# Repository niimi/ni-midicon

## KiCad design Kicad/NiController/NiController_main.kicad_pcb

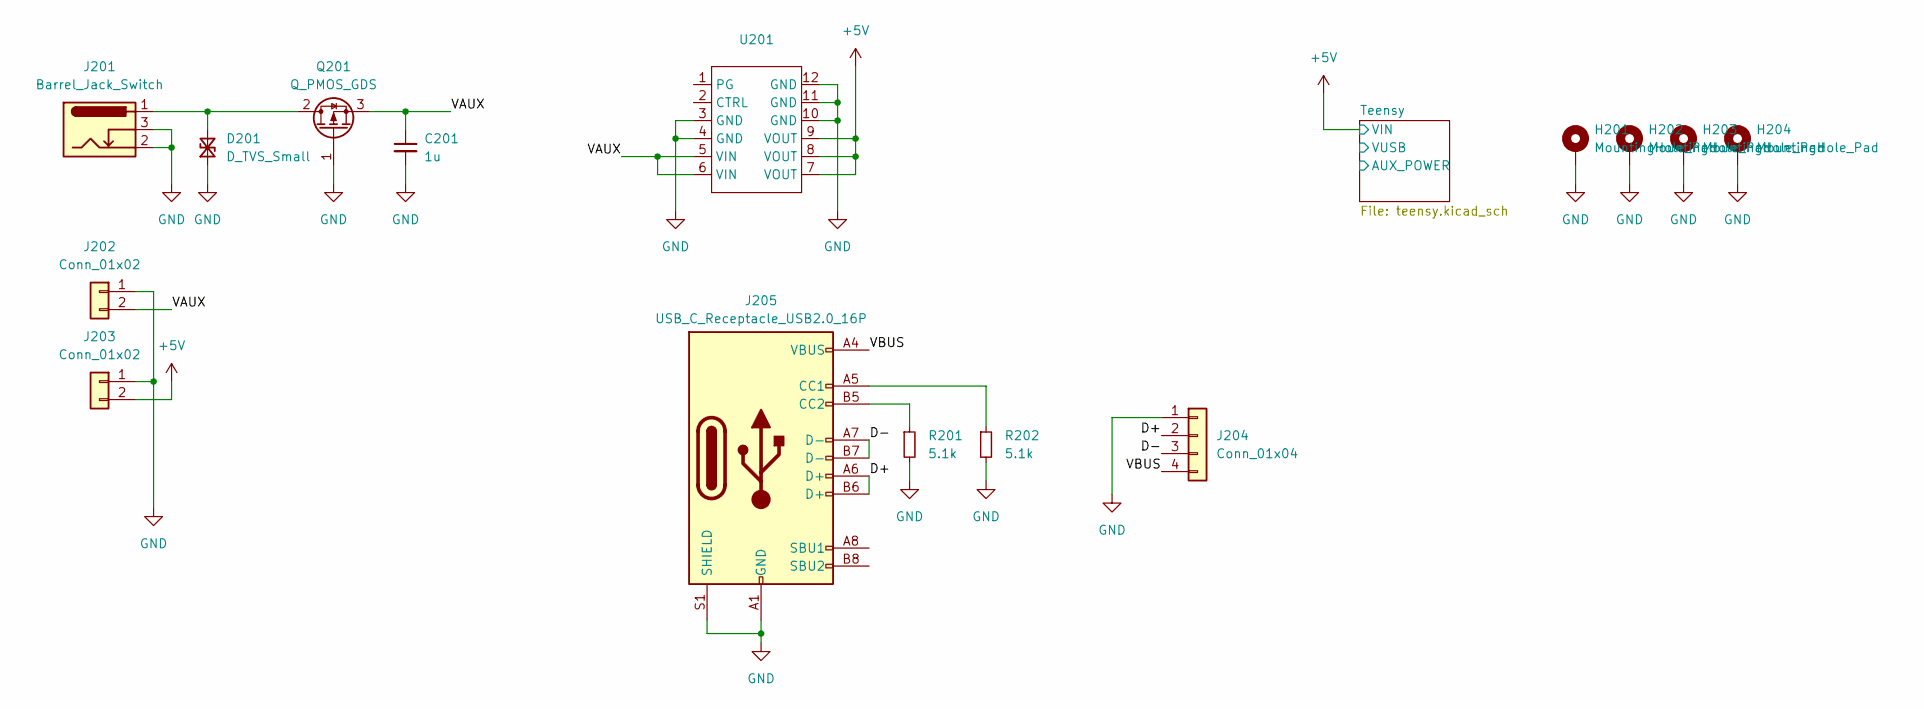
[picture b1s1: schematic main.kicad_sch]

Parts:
C201: 1u; C_0603_1608Metric
D201: D_TVS_Small; D_SOD-523
H201, H202, H203, H204: MountingHole_Pad; MountingHole_2.5mm_Pad_Via
J201: Barrel_Jack_Switch; BarrelJack_Horizontal
J202, J203: Conn_01x02; PinHeader_1x02_P2.54mm_Vertical
J204: Conn_01x04; PinSocket_1x04_P2.54mm_Vertical
J205: USB_C_Receptacle_USB2.0_16P; USB_C_Receptacle_G-Switch_GT-USB-7010ASV
Q201: Q_PMOS_GDS; TO-252-2
R201, R202: 5.1k; R_0603_1608Metric
U201: AE-MYMGK00506ERSR-5V0

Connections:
+5V: J203.2, U201.7 (VOUT), U201.8 (VOUT), U201.9 (VOUT); also elsewhere on the board
/main/D+: J204.2, J205.A6 (D+), J205.B6 (D+)
/main/D-: J204.3, J205.A7 (D-), J205.B7 (D-)
/main/VAUX: C201.1, J202.2, Q201.3 (S), U201.5 (VIN), U201.6 (VIN)
/main/VBUS: J204.4, J205.A4 (VBUS), J205.A9 (VBUS), J205.B4 (VBUS), J205.B9 (VBUS)
GND: C201.2, D201.1 (A1), H201.1, H202.1, H203.1, H204.1, J201.2, J201.3, J202.1, J203.1, J204.1, J205.A1 (GND), J205.A12 (GND), J205.B1 (GND), J205.B12 (GND), J205.S1 (SHIELD), Q201.1 (G), R201.2, R202.2, U201.3 (GND), U201.4 (GND), U201.10 (GND), U201.11 (GND), U201.12 (GND); also elsewhere on the board
unnamed: D201.2 (A2), J201.1, Q201.2 (D)
unnamed: J205.A5 (CC1), R202.1
unnamed: J205.B5 (CC2), R201.1

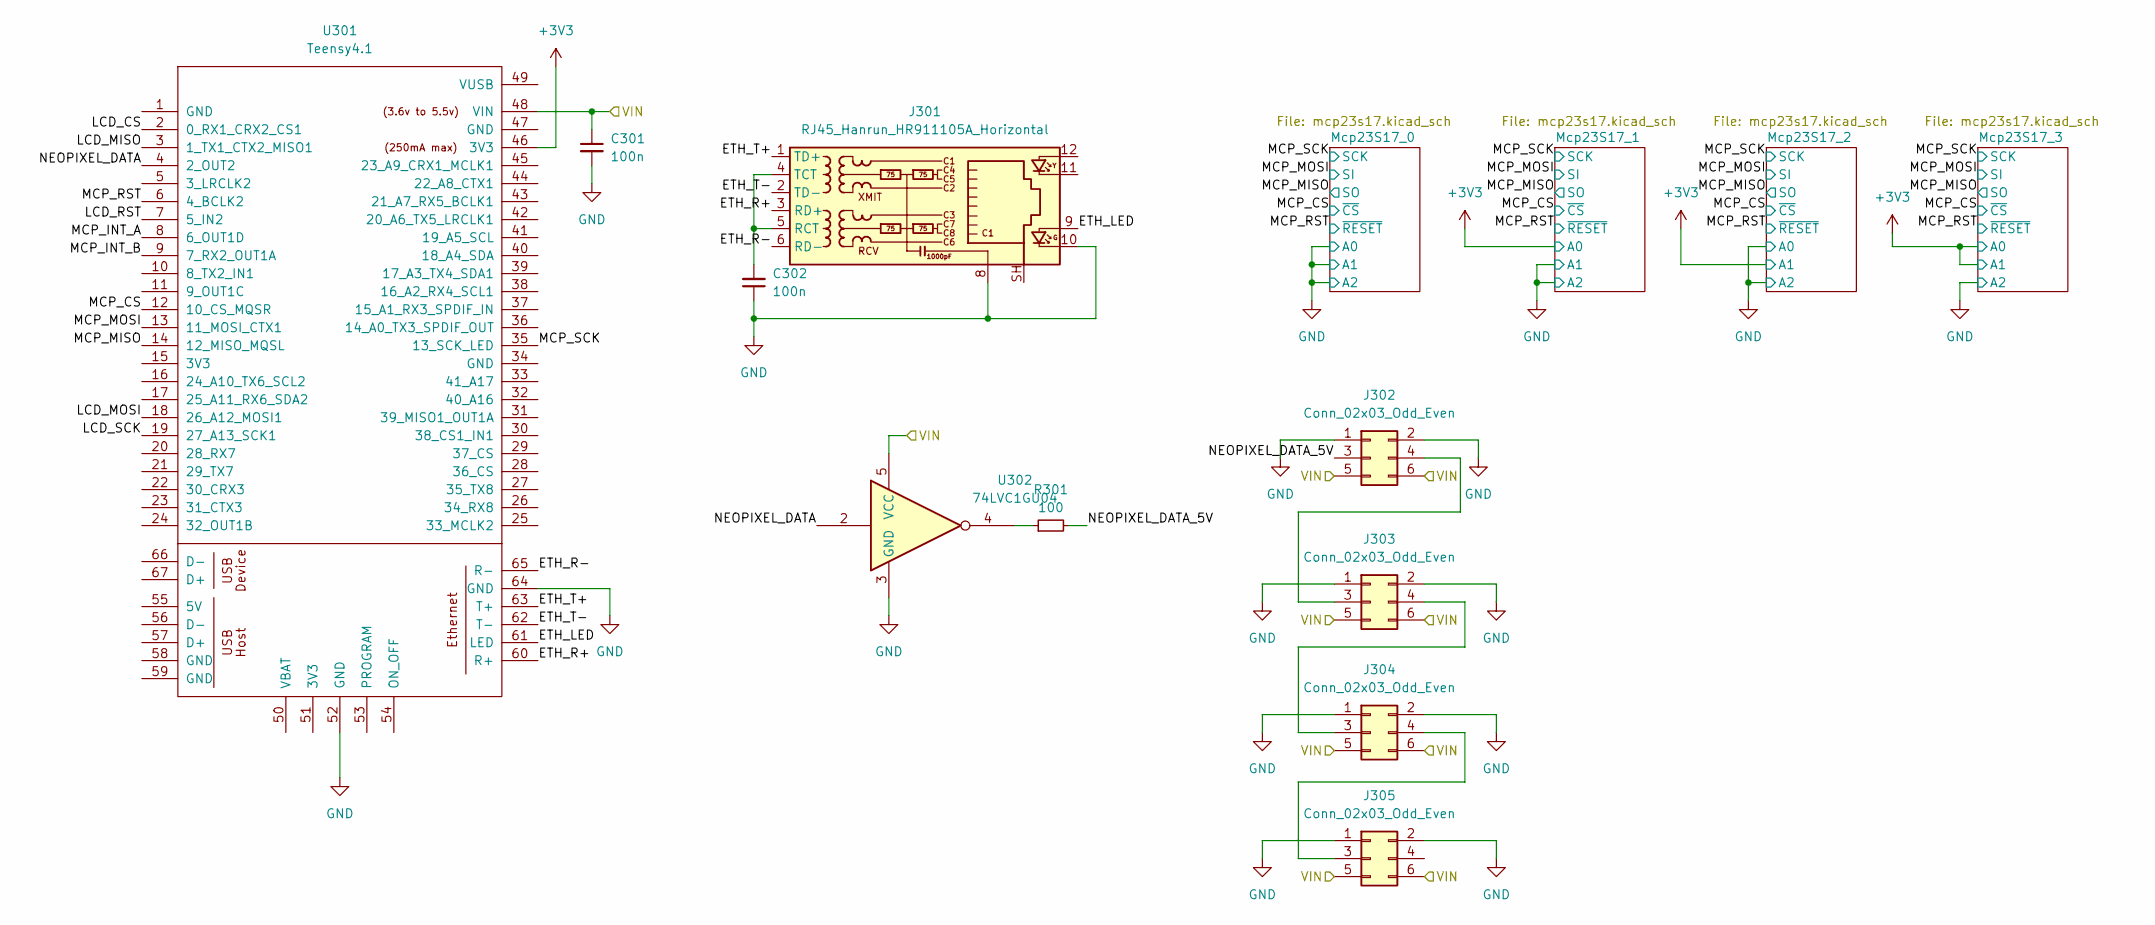
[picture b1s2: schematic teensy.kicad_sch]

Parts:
C301, C302: 100n; C_0603_1608Metric
J301: RJ45_Hanrun_HR911105A_Horizontal
J302, J303, J304, J305: Conn_02x03_Odd_Even; IDC-Header_2x03_P2.54mm_Vertical
R301: 100; R_0603_1608Metric
U301: Teensy4.1; Teensy41
U302: 74LVC1GU04; SOT-353_SC-70-5

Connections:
+3V3: U301.46 (3V3); also elsewhere on the board
+5V: C301.1, J302.5, J302.6, J303.5, J303.6, J304.5, J304.6, J305.5, J305.6, U301.48 (VIN), U302.5 (VCC); also elsewhere on the board
/main/Teensy/ETH_LED: J301.9, U301.61 (LED)
/main/Teensy/ETH_R+: J301.3 (RD+), U301.60 (R+)
/main/Teensy/ETH_R-: J301.6 (RD-), U301.65 (R-)
/main/Teensy/ETH_T+: J301.1 (TD+), U301.63 (T+)
/main/Teensy/ETH_T-: J301.2 (TD-), U301.62 (T-)
/main/Teensy/LCD_CS: U301.2 (0_RX1_CRX2_CS1)
/main/Teensy/LCD_MISO: U301.3 (1_TX1_CTX2_MISO1)
/main/Teensy/LCD_MOSI: U301.18 (26_A12_MOSI1)
/main/Teensy/LCD_RST: U301.7 (5_IN2)
/main/Teensy/LCD_SCK: U301.19 (27_A13_SCK1)
/main/Teensy/MCP_CS: U301.12 (10_CS_MQSR); also elsewhere on the board
/main/Teensy/MCP_INT_A: U301.8 (6_OUT1D)
/main/Teensy/MCP_INT_B: U301.9 (7_RX2_OUT1A)
/main/Teensy/MCP_MISO: U301.14 (12_MISO_MQSL); also elsewhere on the board
/main/Teensy/MCP_MOSI: U301.13 (11_MOSI_CTX1); also elsewhere on the board
/main/Teensy/MCP_RST: U301.6 (4_BCLK2); also elsewhere on the board
/main/Teensy/MCP_SCK: U301.35 (13_SCK_LED); also elsewhere on the board
/main/Teensy/NEOPIXEL_DATA: U301.4 (2_OUT2), U302.2
/main/Teensy/NEOPIXEL_DATA_5V: J302.3, R301.2
GND: C301.2, C302.1, J301.8, J301.10, J302.1, J302.2, J303.1, J303.2, J304.1, J304.2, J305.1, J305.2, U301.52 (GND), U301.64 (GND), U302.3 (GND); also elsewhere on the board
unnamed: C302.2, J301.4 (TCT), J301.5 (RCT)
unnamed: J302.4, J303.3
unnamed: J303.4, J304.3
unnamed: J304.4, J305.3
unnamed: R301.1, U302.4

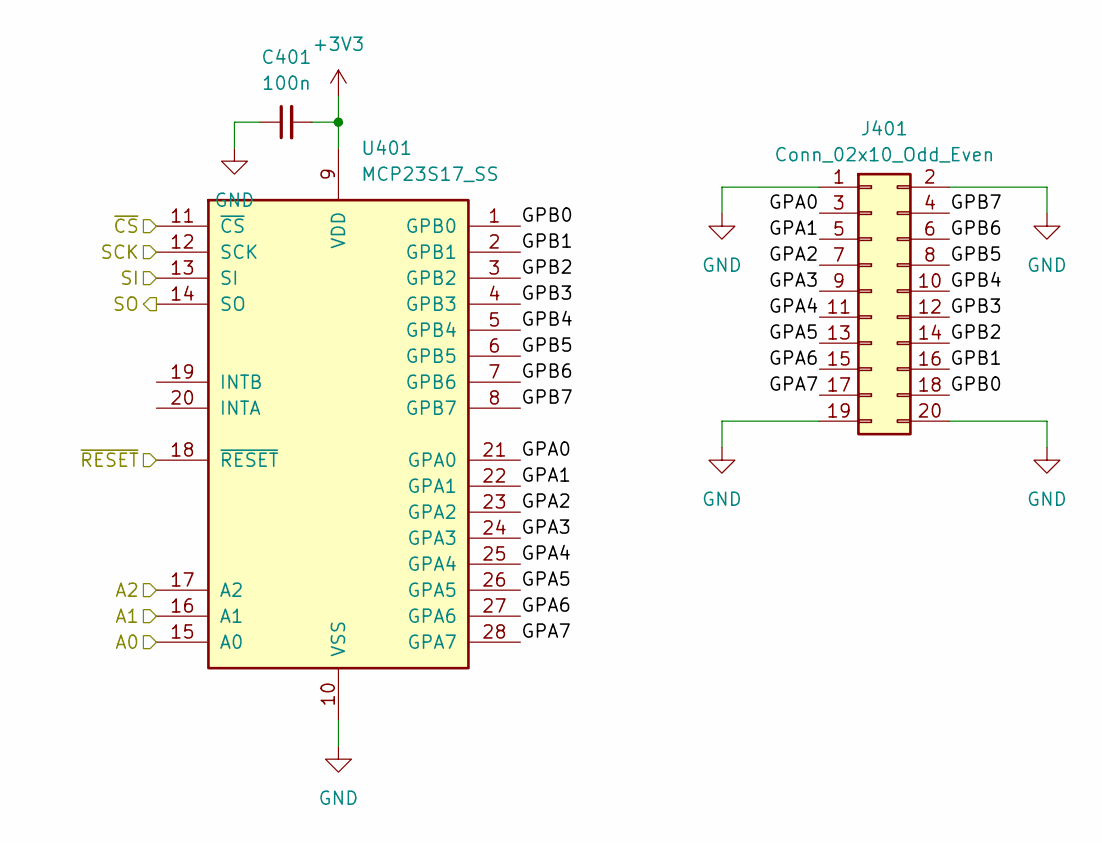
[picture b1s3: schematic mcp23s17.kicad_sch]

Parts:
C401: 100n; C_0603_1608Metric
J401: Conn_02x10_Odd_Even; IDC-Header_2x10_P2.54mm_Vertical
U401: MCP23S17_SS; SSOP-28_5.3x10.2mm_P0.65mm

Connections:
+3V3: C401.2, U401.9 (VDD); also elsewhere on the board
/main/Teensy/MCP_CS: U401.11 (~CS); also elsewhere on the board
/main/Teensy/MCP_MISO: U401.14 (SO); also elsewhere on the board
/main/Teensy/MCP_MOSI: U401.13 (SI); also elsewhere on the board
/main/Teensy/MCP_RST: U401.18 (~RESET); also elsewhere on the board
/main/Teensy/MCP_SCK: U401.12 (SCK); also elsewhere on the board
/main/Teensy/Mcp23S17_0/GPA0: J401.3, U401.21 (GPA0)
/main/Teensy/Mcp23S17_0/GPA1: J401.5, U401.22 (GPA1)
/main/Teensy/Mcp23S17_0/GPA2: J401.7, U401.23 (GPA2)
/main/Teensy/Mcp23S17_0/GPA3: J401.9, U401.24 (GPA3)
/main/Teensy/Mcp23S17_0/GPA4: J401.11, U401.25 (GPA4)
/main/Teensy/Mcp23S17_0/GPA5: J401.13, U401.26 (GPA5)
/main/Teensy/Mcp23S17_0/GPA6: J401.15, U401.27 (GPA6)
/main/Teensy/Mcp23S17_0/GPA7: J401.17, U401.28 (GPA7)
/main/Teensy/Mcp23S17_0/GPB0: J401.18, U401.1 (GPB0)
/main/Teensy/Mcp23S17_0/GPB1: J401.16, U401.2 (GPB1)
/main/Teensy/Mcp23S17_0/GPB2: J401.14, U401.3 (GPB2)
/main/Teensy/Mcp23S17_0/GPB3: J401.12, U401.4 (GPB3)
/main/Teensy/Mcp23S17_0/GPB4: J401.10, U401.5 (GPB4)
/main/Teensy/Mcp23S17_0/GPB5: J401.8, U401.6 (GPB5)
/main/Teensy/Mcp23S17_0/GPB6: J401.6, U401.7 (GPB6)
/main/Teensy/Mcp23S17_0/GPB7: J401.4, U401.8 (GPB7)
GND: C401.1, J401.1, J401.2, J401.19, J401.20, U401.10 (VSS), U401.15 (A0), U401.16 (A1), U401.17 (A2); also elsewhere on the board

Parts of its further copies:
C501, C601, C701: 100n; C_0603_1608Metric
J501, J601, J701: Conn_02x10_Odd_Even; IDC-Header_2x10_P2.54mm_Vertical
U501, U601, U701: MCP23S17_SS; SSOP-28_5.3x10.2mm_P0.65mm

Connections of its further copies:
+3V3: C501.2, C601.2, C701.2, U501.9 (VDD), U501.15 (A0), U601.9 (VDD), U601.16 (A1), U701.9 (VDD), U701.15 (A0), U701.16 (A1); also elsewhere on the board
/main/Teensy/MCP_CS: U501.11 (~CS), U601.11 (~CS), U701.11 (~CS); also elsewhere on the board
/main/Teensy/MCP_MISO: U501.14 (SO), U601.14 (SO), U701.14 (SO); also elsewhere on the board
/main/Teensy/MCP_MOSI: U501.13 (SI), U601.13 (SI), U701.13 (SI); also elsewhere on the board
/main/Teensy/MCP_RST: U501.18 (~RESET), U601.18 (~RESET), U701.18 (~RESET); also elsewhere on the board
/main/Teensy/MCP_SCK: U501.12 (SCK), U601.12 (SCK), U701.12 (SCK); also elsewhere on the board
/main/Teensy/Mcp23S17_1/GPA0: J501.3, U501.21 (GPA0)
/main/Teensy/Mcp23S17_1/GPA1: J501.5, U501.22 (GPA1)
/main/Teensy/Mcp23S17_1/GPA2: J501.7, U501.23 (GPA2)
/main/Teensy/Mcp23S17_1/GPA3: J501.9, U501.24 (GPA3)
/main/Teensy/Mcp23S17_1/GPA4: J501.11, U501.25 (GPA4)
/main/Teensy/Mcp23S17_1/GPA5: J501.13, U501.26 (GPA5)
/main/Teensy/Mcp23S17_1/GPA6: J501.15, U501.27 (GPA6)
/main/Teensy/Mcp23S17_1/GPA7: J501.17, U501.28 (GPA7)
/main/Teensy/Mcp23S17_1/GPB0: J501.18, U501.1 (GPB0)
/main/Teensy/Mcp23S17_1/GPB1: J501.16, U501.2 (GPB1)
/main/Teensy/Mcp23S17_1/GPB2: J501.14, U501.3 (GPB2)
/main/Teensy/Mcp23S17_1/GPB3: J501.12, U501.4 (GPB3)
/main/Teensy/Mcp23S17_1/GPB4: J501.10, U501.5 (GPB4)
/main/Teensy/Mcp23S17_1/GPB5: J501.8, U501.6 (GPB5)
/main/Teensy/Mcp23S17_1/GPB6: J501.6, U501.7 (GPB6)
/main/Teensy/Mcp23S17_1/GPB7: J501.4, U501.8 (GPB7)
/main/Teensy/Mcp23S17_2/GPA0: J601.3, U601.21 (GPA0)
/main/Teensy/Mcp23S17_2/GPA1: J601.5, U601.22 (GPA1)
/main/Teensy/Mcp23S17_2/GPA2: J601.7, U601.23 (GPA2)
/main/Teensy/Mcp23S17_2/GPA3: J601.9, U601.24 (GPA3)
/main/Teensy/Mcp23S17_2/GPA4: J601.11, U601.25 (GPA4)
/main/Teensy/Mcp23S17_2/GPA5: J601.13, U601.26 (GPA5)
/main/Teensy/Mcp23S17_2/GPA6: J601.15, U601.27 (GPA6)
/main/Teensy/Mcp23S17_2/GPA7: J601.17, U601.28 (GPA7)
/main/Teensy/Mcp23S17_2/GPB0: J601.18, U601.1 (GPB0)
/main/Teensy/Mcp23S17_2/GPB1: J601.16, U601.2 (GPB1)
/main/Teensy/Mcp23S17_2/GPB2: J601.14, U601.3 (GPB2)
/main/Teensy/Mcp23S17_2/GPB3: J601.12, U601.4 (GPB3)
/main/Teensy/Mcp23S17_2/GPB4: J601.10, U601.5 (GPB4)
/main/Teensy/Mcp23S17_2/GPB5: J601.8, U601.6 (GPB5)
/main/Teensy/Mcp23S17_2/GPB6: J601.6, U601.7 (GPB6)
/main/Teensy/Mcp23S17_2/GPB7: J601.4, U601.8 (GPB7)
/main/Teensy/Mcp23S17_3/GPA0: J701.3, U701.21 (GPA0)
/main/Teensy/Mcp23S17_3/GPA1: J701.5, U701.22 (GPA1)
/main/Teensy/Mcp23S17_3/GPA2: J701.7, U701.23 (GPA2)
/main/Teensy/Mcp23S17_3/GPA3: J701.9, U701.24 (GPA3)
/main/Teensy/Mcp23S17_3/GPA4: J701.11, U701.25 (GPA4)
/main/Teensy/Mcp23S17_3/GPA5: J701.13, U701.26 (GPA5)
/main/Teensy/Mcp23S17_3/GPA6: J701.15, U701.27 (GPA6)
/main/Teensy/Mcp23S17_3/GPA7: J701.17, U701.28 (GPA7)
/main/Teensy/Mcp23S17_3/GPB0: J701.18, U701.1 (GPB0)
/main/Teensy/Mcp23S17_3/GPB1: J701.16, U701.2 (GPB1)
/main/Teensy/Mcp23S17_3/GPB2: J701.14, U701.3 (GPB2)
/main/Teensy/Mcp23S17_3/GPB3: J701.12, U701.4 (GPB3)
/main/Teensy/Mcp23S17_3/GPB4: J701.10, U701.5 (GPB4)
/main/Teensy/Mcp23S17_3/GPB5: J701.8, U701.6 (GPB5)
/main/Teensy/Mcp23S17_3/GPB6: J701.6, U701.7 (GPB6)
/main/Teensy/Mcp23S17_3/GPB7: J701.4, U701.8 (GPB7)
GND: C501.1, C601.1, C701.1, J501.1, J501.2, J501.19, J501.20, J601.1, J601.2, J601.19, J601.20, J701.1, J701.2, J701.19, J701.20, U501.10 (VSS), U501.16 (A1), U501.17 (A2), U601.10 (VSS), U601.15 (A0), U601.17 (A2), U701.10 (VSS), U701.17 (A2); also elsewhere on the board

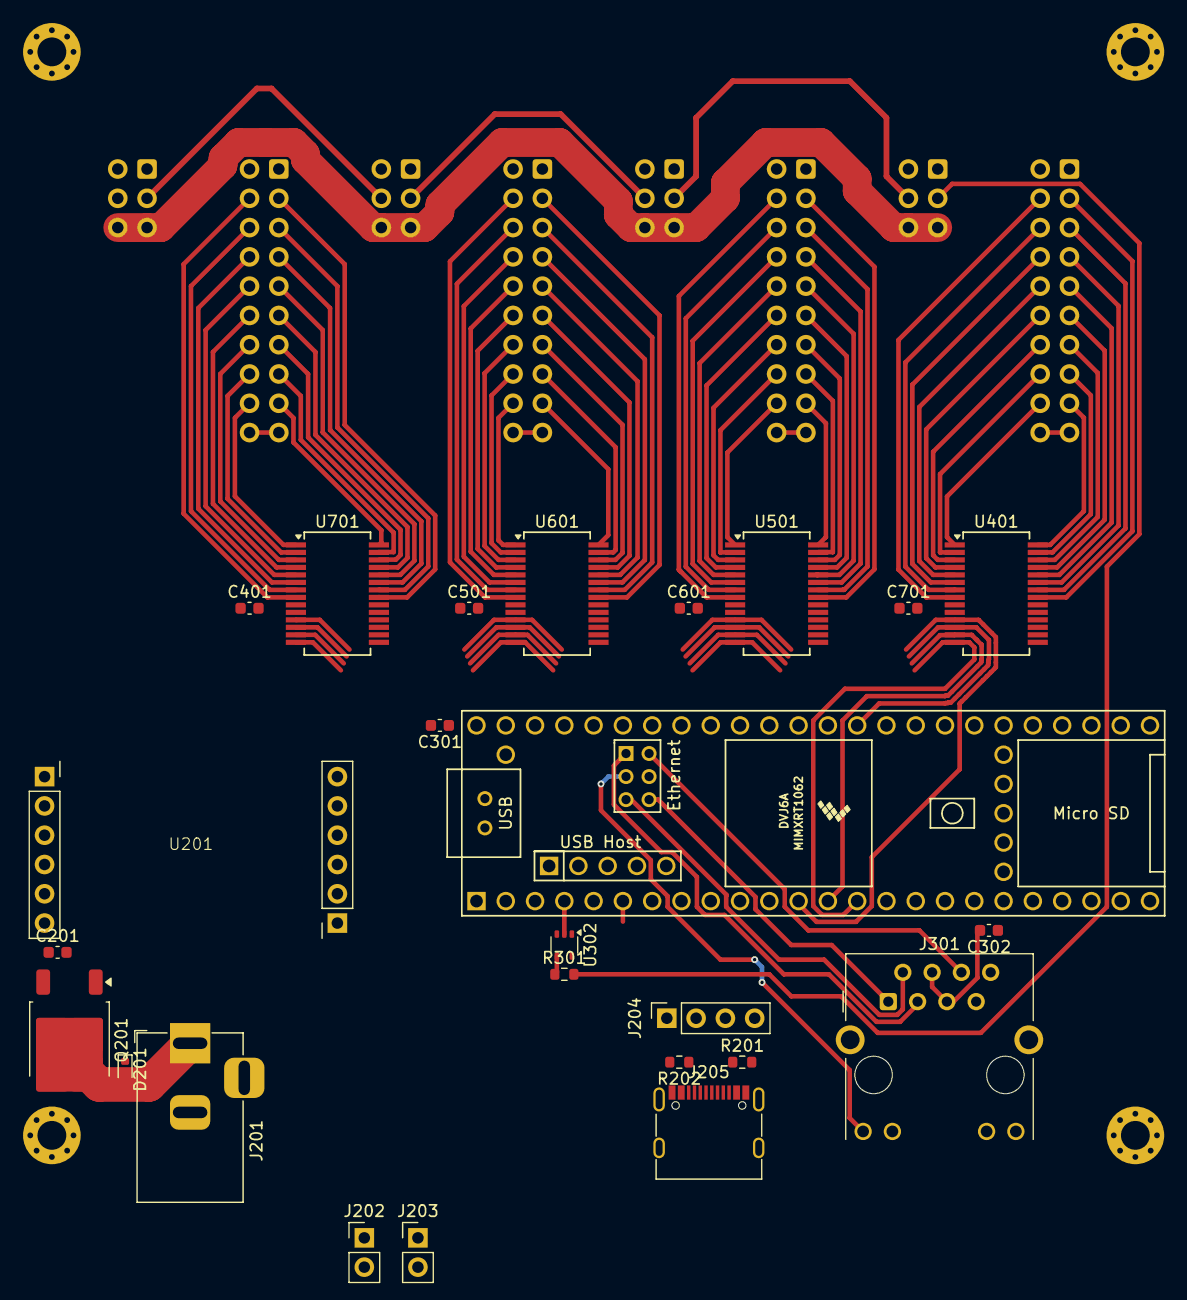
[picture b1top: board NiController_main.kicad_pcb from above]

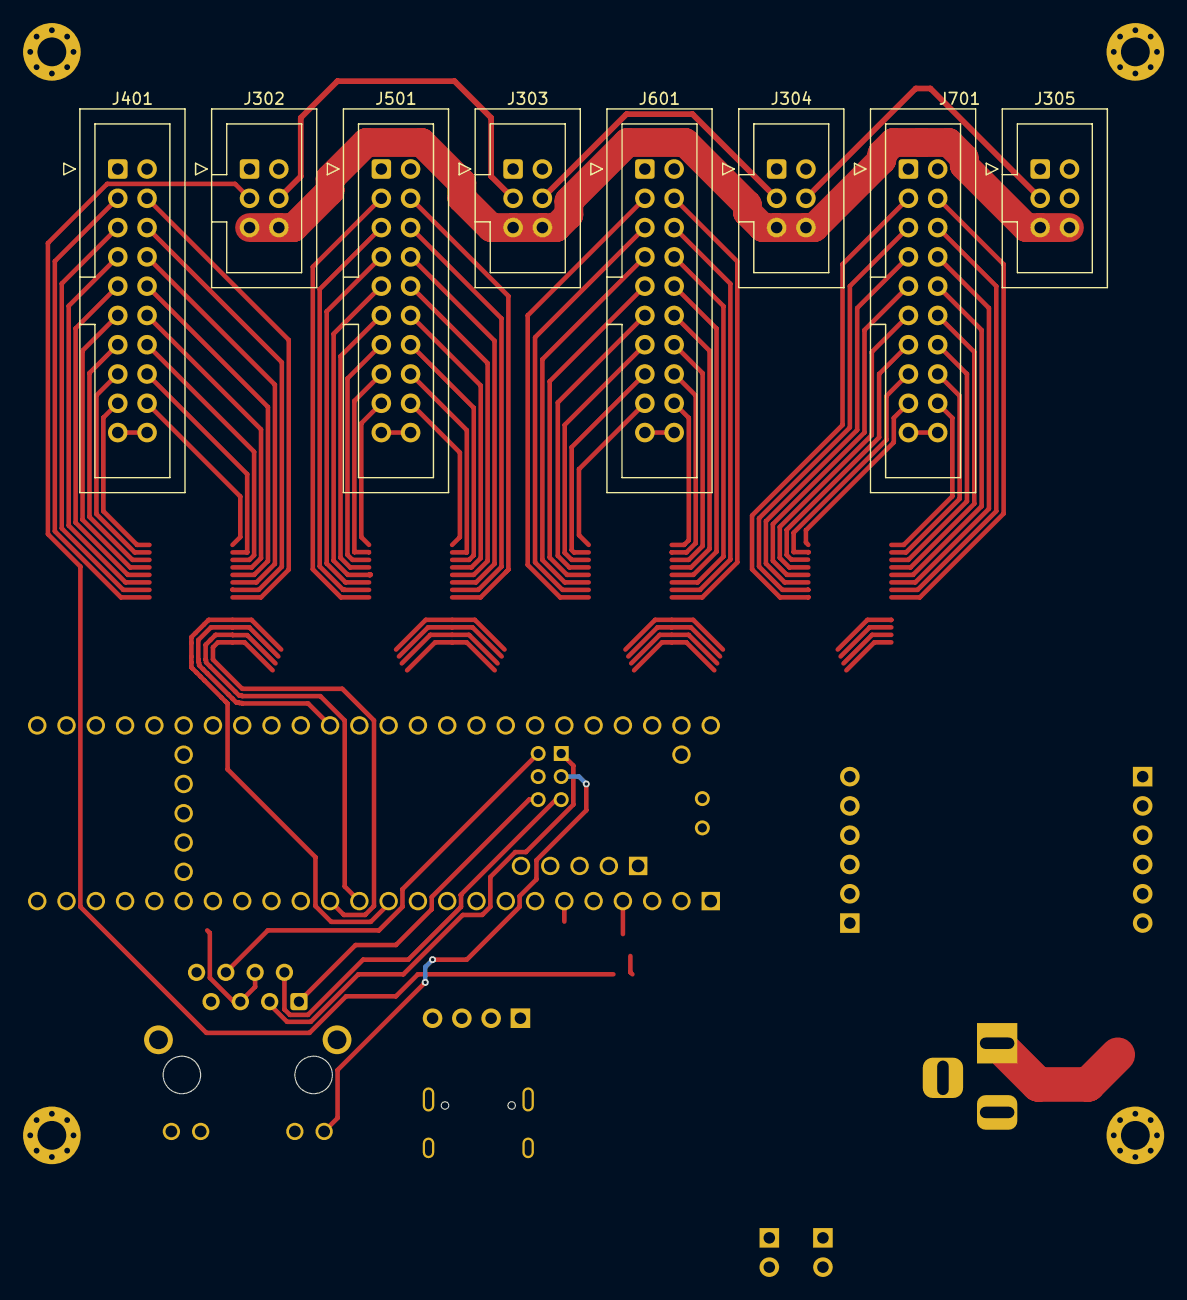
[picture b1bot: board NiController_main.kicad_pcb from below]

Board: 2 copper layers, 37 parts (8 on the bottom side), 91 nets.

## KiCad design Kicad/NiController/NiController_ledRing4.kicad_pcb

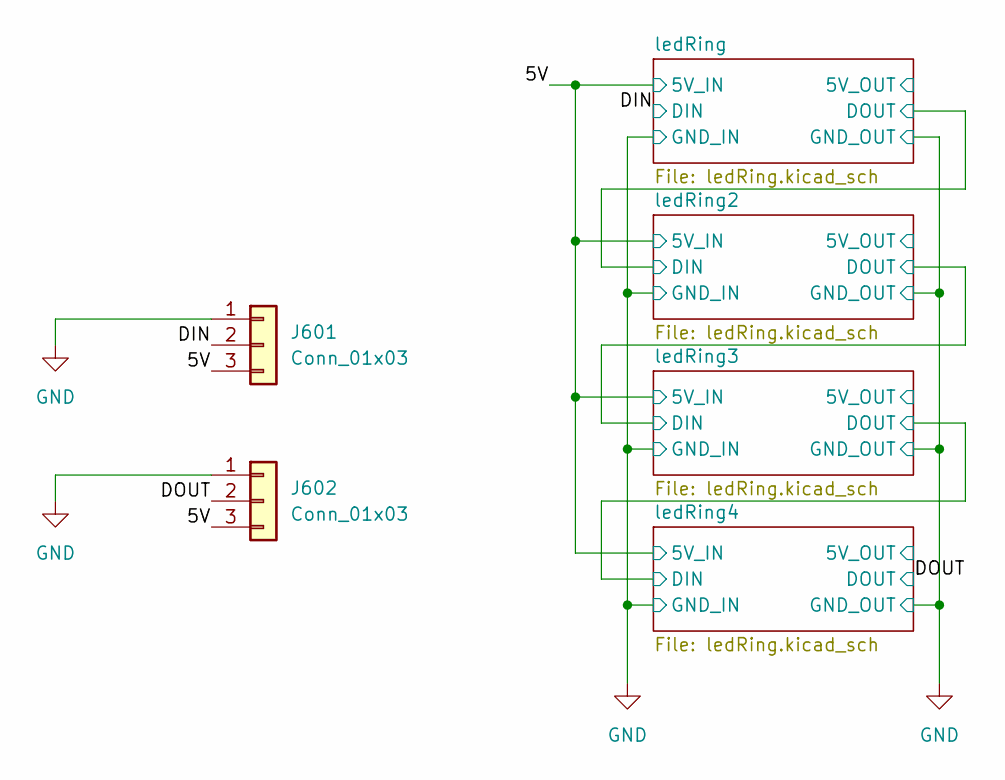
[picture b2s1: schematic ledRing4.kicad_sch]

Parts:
J601, J602: Conn_01x03; PinHeader_1x03_P2.54mm_Vertical

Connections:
+5V: J601.3, J602.3; also elsewhere on the board
/ledRing4/DIN: J601.2; also elsewhere on the board
/ledRing4/DOUT: J602.2; also elsewhere on the board
GND: J601.1, J602.1; also elsewhere on the board

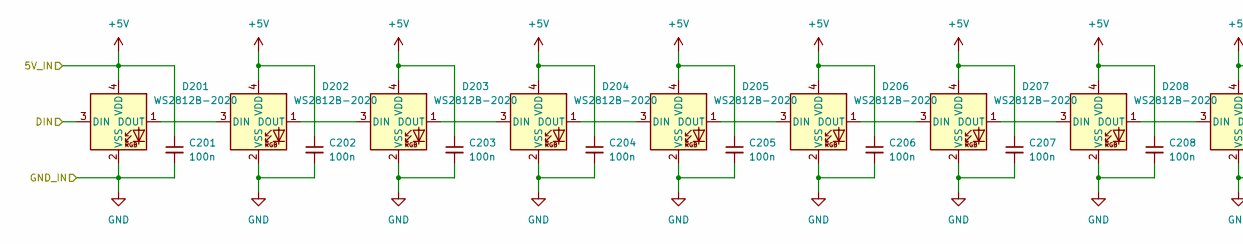
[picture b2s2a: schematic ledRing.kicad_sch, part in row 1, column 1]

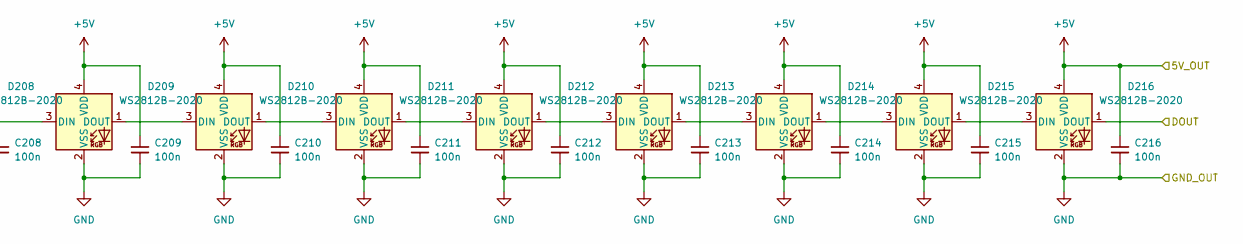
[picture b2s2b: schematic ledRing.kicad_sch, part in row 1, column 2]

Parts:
C201, C202, C203, C204, C205, C206, C207, C208, C209, C210, C211, C212, C213, C214, C215, C216: 100n; C_0603_1608Metric
D201, D202, D203, D204, D205, D206, D207, D208, D209, D210, D211, D212, D213, D214, D215, D216: WS2812B-2020; LED_WS2812B-2020_PLCC4_2.0x2.0mm

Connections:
+5V: C201.1, C202.1, C203.1, C204.1, C205.1, C206.1, C207.1, C208.1, C209.1, C210.1, C211.1, C212.1, C213.1, C214.1, C215.1, C216.1, D201.4 (VDD), D202.4 (VDD), D203.4 (VDD), D204.4 (VDD), D205.4 (VDD), D206.4 (VDD), D207.4 (VDD), D208.4 (VDD), D209.4 (VDD), D210.4 (VDD), D211.4 (VDD), D212.4 (VDD), D213.4 (VDD), D214.4 (VDD), D215.4 (VDD), D216.4 (VDD); also elsewhere on the board
/ledRing4/DIN: D201.3 (DIN); also elsewhere on the board
/ledRing4/ledRing/DOUT: D216.1 (DOUT); also elsewhere on the board
GND: C201.2, C202.2, C203.2, C204.2, C205.2, C206.2, C207.2, C208.2, C209.2, C210.2, C211.2, C212.2, C213.2, C214.2, C215.2, C216.2, D201.2 (VSS), D202.2 (VSS), D203.2 (VSS), D204.2 (VSS), D205.2 (VSS), D206.2 (VSS), D207.2 (VSS), D208.2 (VSS), D209.2 (VSS), D210.2 (VSS), D211.2 (VSS), D212.2 (VSS), D213.2 (VSS), D214.2 (VSS), D215.2 (VSS), D216.2 (VSS); also elsewhere on the board
unnamed: D201.1 (DOUT), D202.3 (DIN)
unnamed: D202.1 (DOUT), D203.3 (DIN)
unnamed: D203.1 (DOUT), D204.3 (DIN)
unnamed: D204.1 (DOUT), D205.3 (DIN)
unnamed: D205.1 (DOUT), D206.3 (DIN)
unnamed: D206.1 (DOUT), D207.3 (DIN)
unnamed: D207.1 (DOUT), D208.3 (DIN)
unnamed: D208.1 (DOUT), D209.3 (DIN)
unnamed: D209.1 (DOUT), D210.3 (DIN)
unnamed: D210.1 (DOUT), D211.3 (DIN)
unnamed: D211.1 (DOUT), D212.3 (DIN)
unnamed: D212.1 (DOUT), D213.3 (DIN)
unnamed: D213.1 (DOUT), D214.3 (DIN)
unnamed: D214.1 (DOUT), D215.3 (DIN)
unnamed: D215.1 (DOUT), D216.3 (DIN)

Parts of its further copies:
C301, C302, C303, C304, C305, C306, C307, C308, C309, C310, C311, C312, C313, C314, C315, C316, C401, C402, C403, C404, C405, C406, C407, C408, C409, C410, C411, C412, C413, C414, C415, C416, C501, C502, C503, C504, C505, C506, C507, C508, C509, C510, C511, C512, C513, C514, C515, C516: 100n; C_0603_1608Metric
D301, D302, D303, D304, D305, D306, D307, D308, D309, D310, D311, D312, D313, D314, D315, D316, D401, D402, D403, D404, D405, D406, D407, D408, D409, D410, D411, D412, D413, D414, D415, D416, D501, D502, D503, D504, D505, D506, D507, D508, D509, D510, D511, D512, D513, D514, D515, D516: WS2812B-2020; LED_WS2812B-2020_PLCC4_2.0x2.0mm

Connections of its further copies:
+5V: C301.1, C302.1, C303.1, C304.1, C305.1, C306.1, C307.1, C308.1, C309.1, C310.1, C311.1, C312.1, C313.1, C314.1, C315.1, C316.1, C401.1, C402.1, C403.1, C404.1, C405.1, C406.1, C407.1, C408.1, C409.1, C410.1, C411.1, C412.1, C413.1, C414.1, C415.1, C416.1, C501.1, C502.1, C503.1, C504.1, C505.1, C506.1, C507.1, C508.1, C509.1, C510.1, C511.1, C512.1, C513.1, C514.1, C515.1, C516.1, D301.4 (VDD), D302.4 (VDD), D303.4 (VDD), D304.4 (VDD), D305.4 (VDD), D306.4 (VDD), D307.4 (VDD), D308.4 (VDD), D309.4 (VDD), D310.4 (VDD), D311.4 (VDD), D312.4 (VDD), D313.4 (VDD), D314.4 (VDD), D315.4 (VDD), D316.4 (VDD), D401.4 (VDD), D402.4 (VDD), D403.4 (VDD), D404.4 (VDD), D405.4 (VDD), D406.4 (VDD), D407.4 (VDD), D408.4 (VDD), D409.4 (VDD), D410.4 (VDD), D411.4 (VDD), D412.4 (VDD), D413.4 (VDD), D414.4 (VDD), D415.4 (VDD), D416.4 (VDD), D501.4 (VDD), D502.4 (VDD), D503.4 (VDD), D504.4 (VDD), D505.4 (VDD), D506.4 (VDD), D507.4 (VDD), D508.4 (VDD), D509.4 (VDD), D510.4 (VDD), D511.4 (VDD), D512.4 (VDD), D513.4 (VDD), D514.4 (VDD), D515.4 (VDD), D516.4 (VDD); also elsewhere on the board
/ledRing4/DOUT: D516.1 (DOUT); also elsewhere on the board
/ledRing4/ledRing2/DOUT: D316.1 (DOUT), D401.3 (DIN)
/ledRing4/ledRing3/DOUT: D416.1 (DOUT), D501.3 (DIN)
/ledRing4/ledRing/DOUT: D301.3 (DIN); also elsewhere on the board
GND: C301.2, C302.2, C303.2, C304.2, C305.2, C306.2, C307.2, C308.2, C309.2, C310.2, C311.2, C312.2, C313.2, C314.2, C315.2, C316.2, C401.2, C402.2, C403.2, C404.2, C405.2, C406.2, C407.2, C408.2, C409.2, C410.2, C411.2, C412.2, C413.2, C414.2, C415.2, C416.2, C501.2, C502.2, C503.2, C504.2, C505.2, C506.2, C507.2, C508.2, C509.2, C510.2, C511.2, C512.2, C513.2, C514.2, C515.2, C516.2, D301.2 (VSS), D302.2 (VSS), D303.2 (VSS), D304.2 (VSS), D305.2 (VSS), D306.2 (VSS), D307.2 (VSS), D308.2 (VSS), D309.2 (VSS), D310.2 (VSS), D311.2 (VSS), D312.2 (VSS), D313.2 (VSS), D314.2 (VSS), D315.2 (VSS), D316.2 (VSS), D401.2 (VSS), D402.2 (VSS), D403.2 (VSS), D404.2 (VSS), D405.2 (VSS), D406.2 (VSS), D407.2 (VSS), D408.2 (VSS), D409.2 (VSS), D410.2 (VSS), D411.2 (VSS), D412.2 (VSS), D413.2 (VSS), D414.2 (VSS), D415.2 (VSS), D416.2 (VSS), D501.2 (VSS), D502.2 (VSS), D503.2 (VSS), D504.2 (VSS), D505.2 (VSS), D506.2 (VSS), D507.2 (VSS), D508.2 (VSS), D509.2 (VSS), D510.2 (VSS), D511.2 (VSS), D512.2 (VSS), D513.2 (VSS), D514.2 (VSS), D515.2 (VSS), D516.2 (VSS); also elsewhere on the board
unnamed: D301.1 (DOUT), D302.3 (DIN)
unnamed: D302.1 (DOUT), D303.3 (DIN)
unnamed: D303.1 (DOUT), D304.3 (DIN)
unnamed: D304.1 (DOUT), D305.3 (DIN)
unnamed: D305.1 (DOUT), D306.3 (DIN)
unnamed: D306.1 (DOUT), D307.3 (DIN)
unnamed: D307.1 (DOUT), D308.3 (DIN)
unnamed: D308.1 (DOUT), D309.3 (DIN)
unnamed: D309.1 (DOUT), D310.3 (DIN)
unnamed: D310.1 (DOUT), D311.3 (DIN)
unnamed: D311.1 (DOUT), D312.3 (DIN)
unnamed: D312.1 (DOUT), D313.3 (DIN)
unnamed: D313.1 (DOUT), D314.3 (DIN)
unnamed: D314.1 (DOUT), D315.3 (DIN)
unnamed: D315.1 (DOUT), D316.3 (DIN)
unnamed: D401.1 (DOUT), D402.3 (DIN)
unnamed: D402.1 (DOUT), D403.3 (DIN)
unnamed: D403.1 (DOUT), D404.3 (DIN)
unnamed: D404.1 (DOUT), D405.3 (DIN)
unnamed: D405.1 (DOUT), D406.3 (DIN)
unnamed: D406.1 (DOUT), D407.3 (DIN)
unnamed: D407.1 (DOUT), D408.3 (DIN)
unnamed: D408.1 (DOUT), D409.3 (DIN)
unnamed: D409.1 (DOUT), D410.3 (DIN)
unnamed: D410.1 (DOUT), D411.3 (DIN)
unnamed: D411.1 (DOUT), D412.3 (DIN)
unnamed: D412.1 (DOUT), D413.3 (DIN)
unnamed: D413.1 (DOUT), D414.3 (DIN)
unnamed: D414.1 (DOUT), D415.3 (DIN)
unnamed: D415.1 (DOUT), D416.3 (DIN)
unnamed: D501.1 (DOUT), D502.3 (DIN)
unnamed: D502.1 (DOUT), D503.3 (DIN)
unnamed: D503.1 (DOUT), D504.3 (DIN)
unnamed: D504.1 (DOUT), D505.3 (DIN)
unnamed: D505.1 (DOUT), D506.3 (DIN)
unnamed: D506.1 (DOUT), D507.3 (DIN)
unnamed: D507.1 (DOUT), D508.3 (DIN)
unnamed: D508.1 (DOUT), D509.3 (DIN)
unnamed: D509.1 (DOUT), D510.3 (DIN)
unnamed: D510.1 (DOUT), D511.3 (DIN)
unnamed: D511.1 (DOUT), D512.3 (DIN)
unnamed: D512.1 (DOUT), D513.3 (DIN)
unnamed: D513.1 (DOUT), D514.3 (DIN)
unnamed: D514.1 (DOUT), D515.3 (DIN)
unnamed: D515.1 (DOUT), D516.3 (DIN)

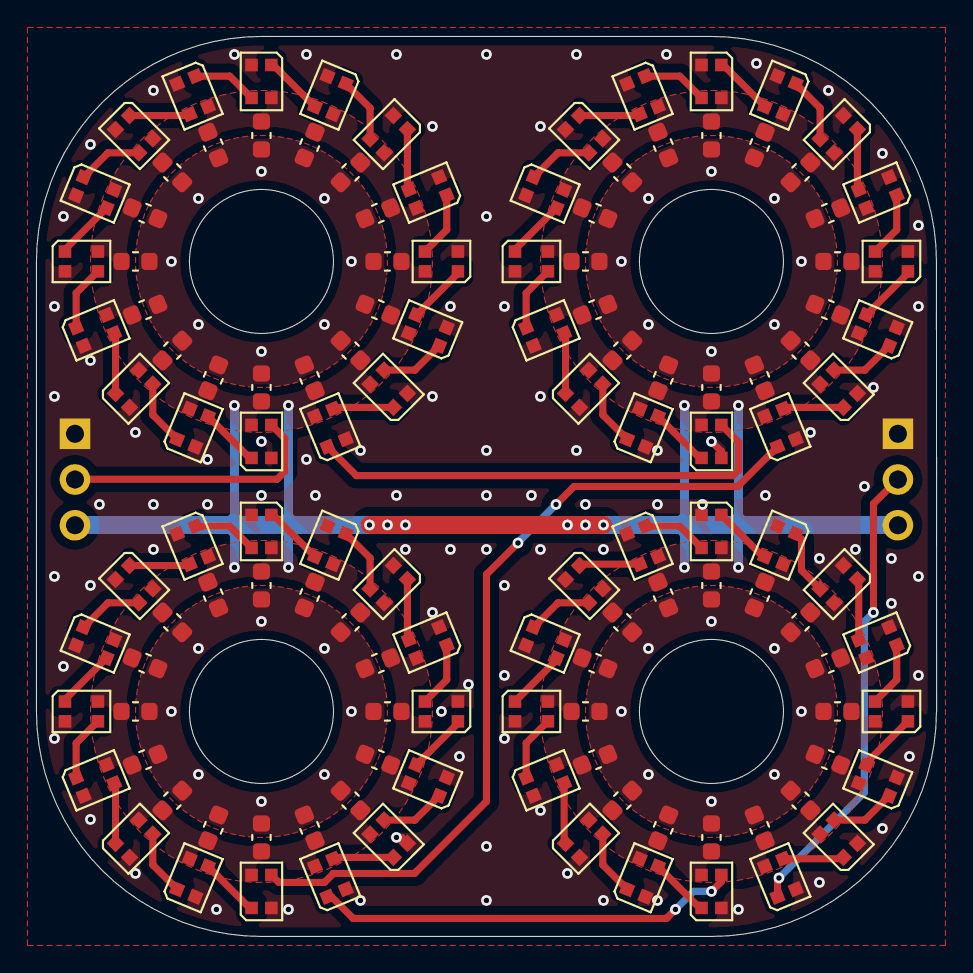
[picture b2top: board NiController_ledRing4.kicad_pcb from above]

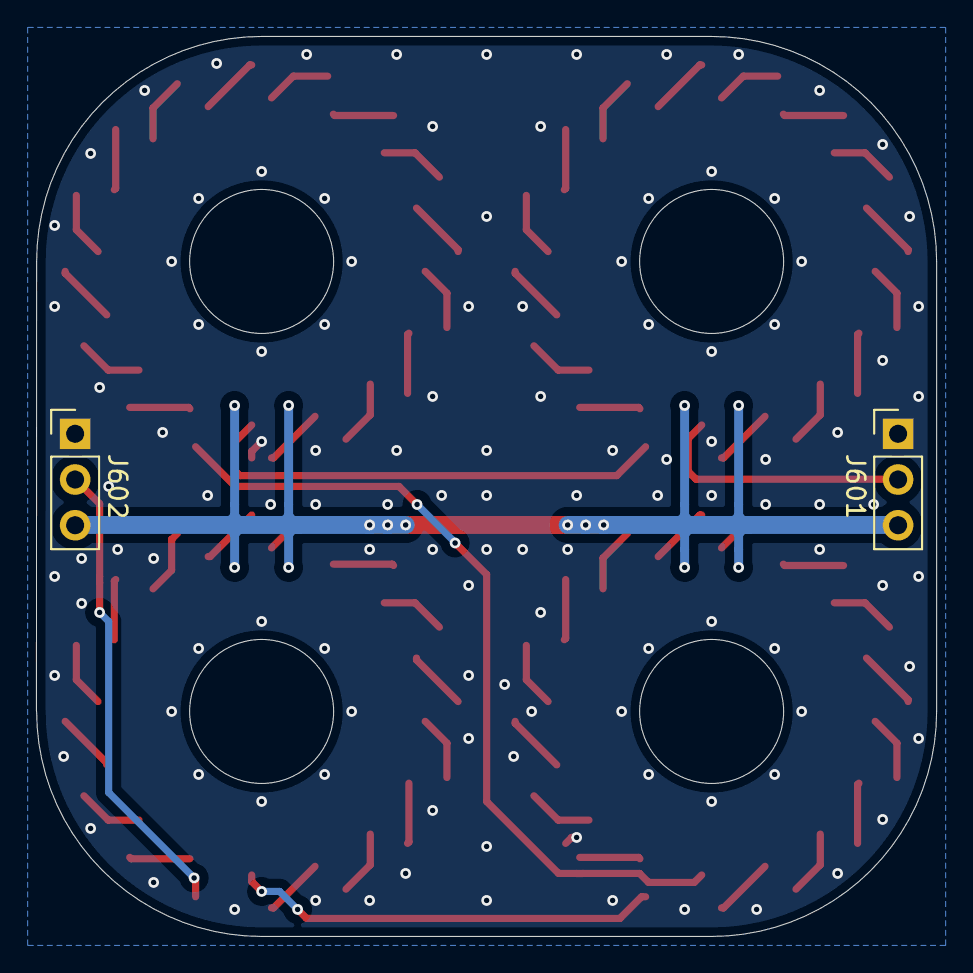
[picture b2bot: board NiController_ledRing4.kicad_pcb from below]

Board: 2 copper layers, 50.0 x 50.0 mm, 130 parts (2 on the bottom side), 67 nets.

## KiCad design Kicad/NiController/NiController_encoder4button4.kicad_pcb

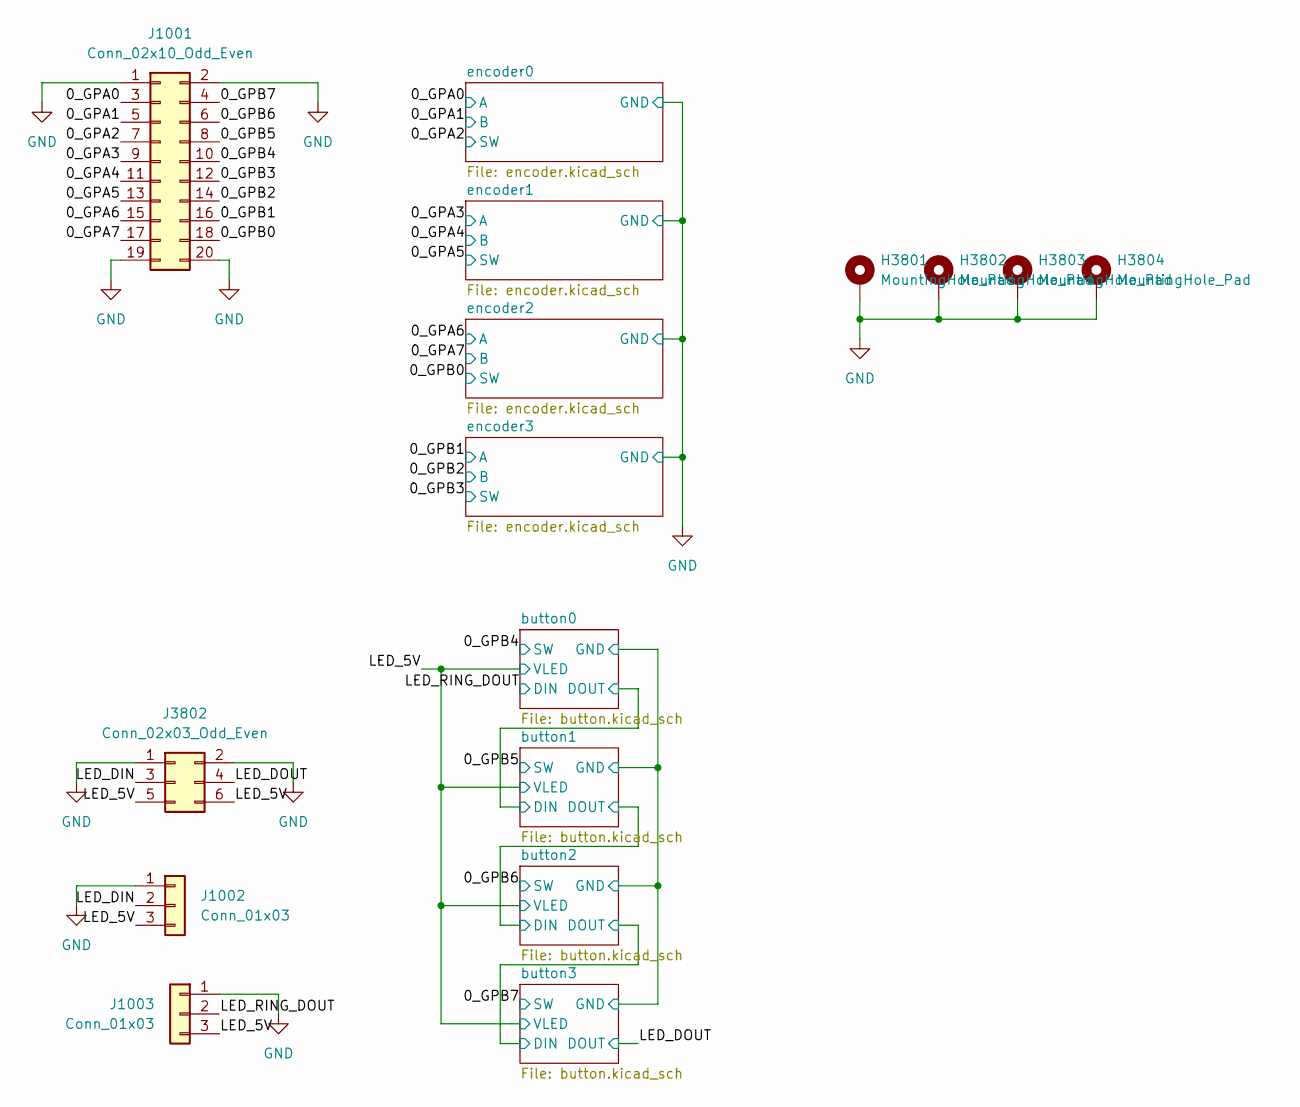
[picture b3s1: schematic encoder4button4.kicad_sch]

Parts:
H3801, H3802, H3803, H3804: MountingHole_Pad; MountingHole_2.5mm_Pad_Via
J1001: Conn_02x10_Odd_Even; IDC-Header_2x10_P2.54mm_Vertical
J1002, J1003: Conn_01x03; PinSocket_1x03_P2.54mm_Vertical
J3802: Conn_02x03_Odd_Even; IDC-Header_2x03_P2.54mm_Vertical

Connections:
/encoder4button4/0_GPA0: J1001.3; also elsewhere on the board
/encoder4button4/0_GPA1: J1001.5; also elsewhere on the board
/encoder4button4/0_GPA2: J1001.7; also elsewhere on the board
/encoder4button4/0_GPA3: J1001.9; also elsewhere on the board
/encoder4button4/0_GPA4: J1001.11; also elsewhere on the board
/encoder4button4/0_GPA5: J1001.13; also elsewhere on the board
/encoder4button4/0_GPA6: J1001.15; also elsewhere on the board
/encoder4button4/0_GPA7: J1001.17; also elsewhere on the board
/encoder4button4/0_GPB0: J1001.18; also elsewhere on the board
/encoder4button4/0_GPB1: J1001.16; also elsewhere on the board
/encoder4button4/0_GPB2: J1001.14; also elsewhere on the board
/encoder4button4/0_GPB3: J1001.12; also elsewhere on the board
/encoder4button4/0_GPB4: J1001.10; also elsewhere on the board
/encoder4button4/0_GPB5: J1001.8; also elsewhere on the board
/encoder4button4/0_GPB6: J1001.6; also elsewhere on the board
/encoder4button4/0_GPB7: J1001.4; also elsewhere on the board
/encoder4button4/LED_5V: J1002.3, J1003.3, J3802.5, J3802.6; also elsewhere on the board
/encoder4button4/LED_DIN: J1002.2, J3802.3
/encoder4button4/LED_DOUT: J3802.4; also elsewhere on the board
/encoder4button4/LED_RING_DOUT: J1003.2; also elsewhere on the board
GND: H3801.1, H3802.1, H3803.1, H3804.1, J1001.1, J1001.2, J1001.19, J1001.20, J1002.1, J1003.1, J3802.1, J3802.2; also elsewhere on the board
